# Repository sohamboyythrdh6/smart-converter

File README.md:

# smart-converter
i made a simpel but really useful stuff to control any ac electronic components by motion like it will mainly used for lights specaly for those peoples who forgot to turnoff the light and their bill goes skyrocket. it is really simpel to use just plug live wire in it then connect bulb AC nutral directly .and put live wire into the sensore and connect bulb live on other point. basicaly when the motion detected the transistor turn the rellay on and the light goes on .the whole circuite powerd by a Hi-link HLK-PM01.

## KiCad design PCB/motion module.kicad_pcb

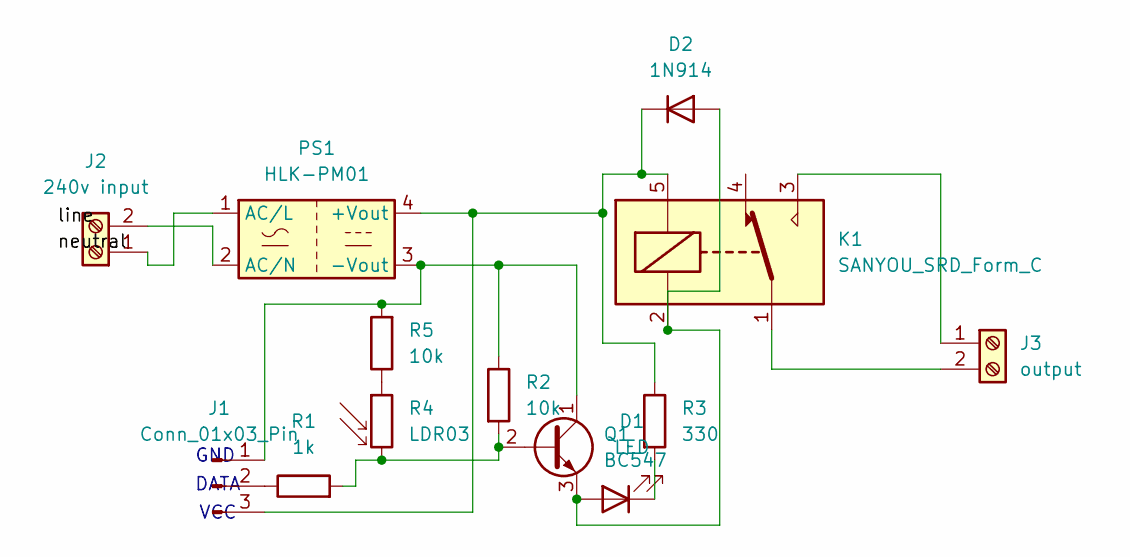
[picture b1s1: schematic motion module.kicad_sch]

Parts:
D1: LED; LED_D5.0mm_Clear
D2: 1N914; D_DO-35_SOD27_P7.62mm_Horizontal
J1: Conn_01x03_Pin; PinSocket_1x03_P2.54mm_Vertical
J2: 240v input; TerminalBlock_MaiXu_MX126-5.0-02P_1x02_P5.00mm
J3: output; TerminalBlock_MaiXu_MX126-5.0-02P_1x02_P5.00mm
K1: SANYOU_SRD_Form_C; Relay_SPDT_SANYOU_SRD_Series_Form_C
PS1: HLK-PM01; Converter_ACDC_Hi-Link_HLK-PMxx
Q1: BC547; TO-92_Inline
R1: 1k; R_Axial_DIN0204_L3.6mm_D1.6mm_P5.08mm_Horizontal
R2, R5: 10k; R_Axial_DIN0204_L3.6mm_D1.6mm_P5.08mm_Horizontal
R3: 330; R_Axial_DIN0204_L3.6mm_D1.6mm_P5.08mm_Horizontal
R4: LDR03; R_LDR_10x8.5mm_P7.6mm_Vertical

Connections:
unnamed: D1.2 (A), D2.2 (A), K1.2, Q1.3 (E)
unnamed: D1.1 (K), R3.2
unnamed: D2.1 (K), J1.3, K1.5, PS1.4 (+Vout), R3.1
unnamed: J1.1, PS1.3 (-Vout), Q1.1 (C), R2.1, R5.2
unnamed: J1.2, R1.1
unnamed: J2.1, PS1.1 (AC/L)
unnamed: J2.2, PS1.2 (AC/N)
unnamed: J3.1, K1.3
unnamed: J3.2, K1.1
unnamed: Q1.2 (B), R1.2, R2.2, R4.2
unnamed: R4.1, R5.1

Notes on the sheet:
VCC
GND
DATA

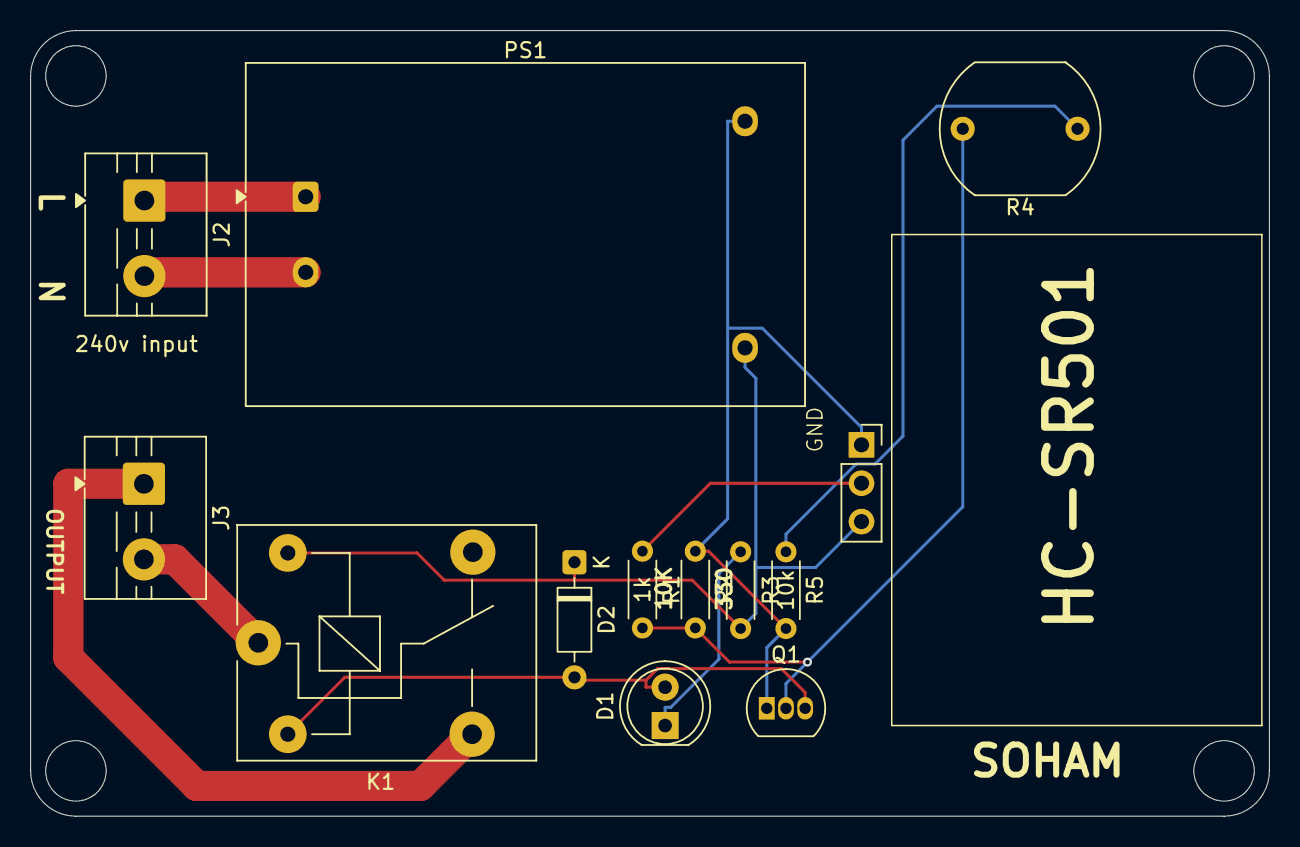
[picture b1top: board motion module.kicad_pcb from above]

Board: 2 copper layers, 82.0 x 52.0 mm, 13 parts (0 on the bottom side), 11 nets.

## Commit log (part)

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2026-05-10 Fix typos and improve clarity in README.md
    Corrected spelling and grammatical errors in the README.
2026-05-10 Create j
2026-05-10 Create 8
2026-05-10 Rename gerber.rar to gerber.zip
2026-05-11 Create F
2026-05-11 Create 4
2026-05-11 Create B
2026-05-11 Rename Zine.png.png to Zine.png
2026-05-12 Fix delivery charges entry in BOM.csv
2026-05-30 Create a
